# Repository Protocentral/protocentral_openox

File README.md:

Protocentral OpenOx Wireless Pulse Sensor Kit based on AFE4400/ESP32
========================================

## Don't have one? [Buy it here](https://protocentral.com/product/protocentral-openox-pulse-oximeter-breakout-board-kit/)

Protocentral OpenOx is a new standalone, wireless pulse oximetry breakout board that is powered by the ubiquitous ESP32 WROOM32 module and uses the AFE4490 IC to measure oxygen levels in the blood while also providing a PPG waveform, heart rate, and SpO2 values measured with high precision. 

Protocentral OpenOx redefines mobility and wireless capabilities. It functions as a data acquisition system, allowing for continuous real-time monitoring of blood oxygen levels via BLE, which improves the user's medical care within his or her environment as well as medical research opportunities. The standard Nellcor probe is used, which is comfortable to wear, does not restrict the user's freedom of movement, and functions as a battery-powered standalone device.

## Hardware Setup

Connection with the Arduino board is as follows:

 |OpenOx pin label| Arduino Connection  |Pin Function      |
 |:-----------------: |:---------------------:|:------------------:|
 | Tx0              |  -                       |  Serial Data     |
 | RX0              |  -                        |  Serial Clock    |
 | SDA              |  SDA                        |  Power           |
 | SCL              |  SCL                      |  GND             |
 | GND              | GND                     |  Ground          |
 | 3V3              | 3V                      |  3V power supply |

# Visualizing Output

### USB Streaming

* Open the GUI, make sure to select **AFE4490 breakout** under the **Board** dropdown and the appropriate **Port**. If everything goes well, you will be able to see the screen as pictured above.

   <center>

  </center>

### BLE streaming

 <center>

  </center>

 <center>

  </center>

## For further details, refer [the documentation on OpenOx Wireless Pulse Sensor](https://docs.protocentral.com/getting-started-with-openox/)

License Information
===================

This product is open source! Both, our hardware and software are open source and licensed under the following licenses:

Hardware
---------

**All hardware is released under the [CERN-OHL-P v2](https://ohwr.org/cern_ohl_p_v2.txt)** license.

Copyright CERN 2020.

This source describes Open Hardware and is licensed under the CERN-OHL-P v2.

You may redistribute and modify this documentation and make products
using it under the terms of the CERN-OHL-P v2 (https:/cern.ch/cern-ohl).
This documentation is distributed WITHOUT ANY EXPRESS OR IMPLIED
WARRANTY, INCLUDING OF MERCHANTABILITY, SATISFACTORY QUALITY
AND FITNESS FOR A PARTICULAR PURPOSE. Please see the CERN-OHL-P v2
for applicable conditions

Software
--------

**All software is released under the MIT License(http://opensource.org/licenses/MIT).**

THE SOFTWARE IS PROVIDED "AS IS", WITHOUT WARRANTY OF ANY KIND, EXPRESS OR IMPLIED, INCLUDING BUT NOT LIMITED TO THE WARRANTIES OF MERCHANTABILITY, FITNESS FOR A PARTICULAR PURPOSE AND NONINFRINGEMENT. IN NO EVENT SHALL THE AUTHORS OR COPYRIGHT HOLDERS BE LIABLE FOR ANY CLAIM, DAMAGES OR OTHER LIABILITY, WHETHER IN AN ACTION OF CONTRACT, TORT OR OTHERWISE, ARISING FROM, OUT OF OR IN CONNECTION WITH THE SOFTWARE OR THE USE OR OTHER DEALINGS IN THE SOFTWARE.

Documentation
-------------
**All documentation is released under [Creative Commons Share-alike 4.0 International](http://creativecommons.org/licenses/by-sa/4.0/).**

You are free to:

* Share — copy and redistribute the material in any medium or format
* Adapt — remix, transform, and build upon the material for any purpose, even commercially.
The licensor cannot revoke these freedoms as long as you follow the license terms.

Under the following terms:

* Attribution — You must give appropriate credit, provide a link to the license, and indicate if changes were made. You may do so in any reasonable manner, but not in any way that suggests the licensor endorses you or your use.
* ShareAlike — If you remix, transform, or build upon the material, you must distribute your contributions under the same license as the original.

Please check [*LICENSE.md*](LICENSE.md) for detailed license descriptions.

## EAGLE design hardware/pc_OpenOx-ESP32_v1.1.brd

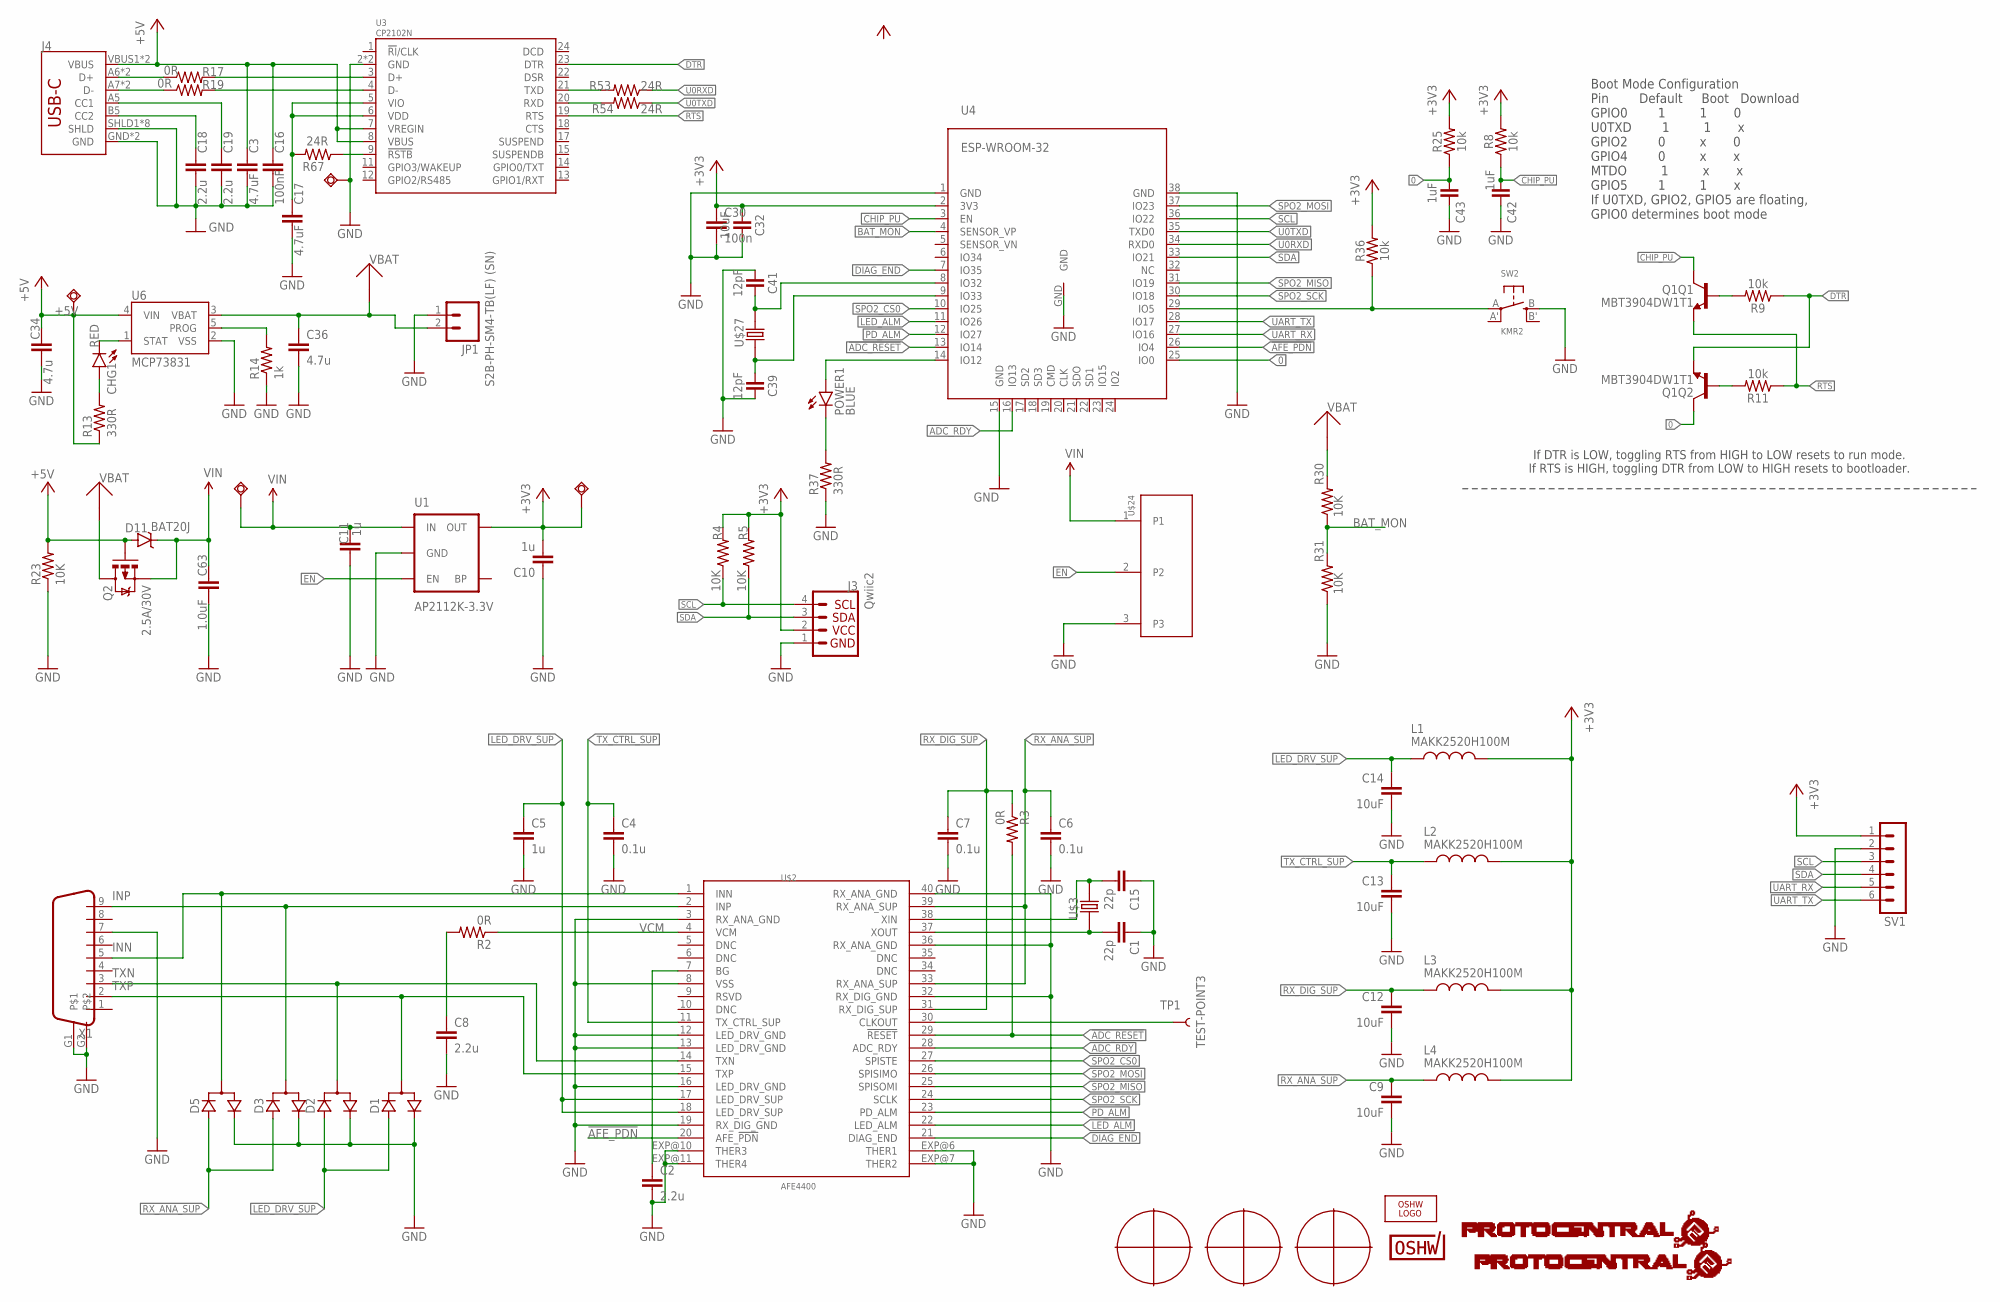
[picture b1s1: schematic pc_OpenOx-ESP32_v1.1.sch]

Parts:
C1, C15: 22p; C0402
C2, C8, C18, C19: 2.2u; C0402
C3, C17: 4.7uF; C0402
C4, C6, C7: 0.1u; C0805
C5, C10, C11: 1u; C0805
C9, C12, C13, C14, C32: 10uF; C0805
C16: 100nF; C0402
C30: 100n; C0805
C34, C36: 4.7u; C0805
C39, C41: 12pF; C0402
C42, C43: 1uF; C0402
C63: 1.0uF; C0402
CHG1: RED; CHIPLED_0603
D1, D2, D3, D5: D_ACACSOT323; SOT323
D11: BAT20J; SOD-323
J3: Qwiic2; 1X04_1MM_RA
J4: USB_C2-LAYER; USB-C-16P
JP1: S2B-PH-SM4-TB(LF) (SN); JST-2-SMD
L1, L2, L3, L4: MAKK2520H100M; INDC2520X100N
LOGO2: OSHW_LOGO_FILLX0200-NT; OSHW_FILLX200_NOTEXT
POWER1: BLUE; CHIPLED_0603
Q1: MBT3904DW1T1; SC70-6
Q2: 2.5A/30V; SOT23-3
R2, R17, R19: 0R; R0402
R3: 0R; R0805
R4, R5, R23, R30, R31: 10K; R0402
R8, R9, R11, R25, R36: 10k; 0603
R13, R37: 330R; R0402
R14: 1k; R0402
R53, R54, R67: 24R; R0402
SV1: MA06-1
SW2: KMR2; BTN_KMR2_4.6X2.8
SWIO1, SWIO2, SWIO3, SWIO17: TPSQTP13R; TP13R
TP1: TEST-POINT3; PAD.03X.03
U1: AP2112K-3.3V; SOT23-5
U3: CP2102N; QFN24
U4: ESP-WROOM-32
U6: MCP73831; SOT23-5
U$2: AFE4400; QFN-40
U$3: ABM3
U$4: PROTY_LOGO_WITH_TEXT; PROTY_WITH_TEXT
U$5: PROTY-LOGO; LOGO-PROTY
U$7: CERT-SMALL; CERT-SMALL-SILK
U$24: JS102011SCQN
U$27: 520-327-12.5-34B(32.768KHZ); ECX-31B
U$33, U$34, U$35: FUDCIALPOINTS; FIDUCIALPOINTS
X1: DB9

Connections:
0: C43.1, Q1.6 (C), R25.1, U4.25 (IO0)
3.3V: C17.1, R67.2, U3.5 (VIO), U3.6 (VDD)
!ADC_RESET: R3.2, U4.13 (IO14), U$2.29 (!RESET)
!AFE_PDN: U4.26 (IO4), U$2.20 (AFE_!PDN)
+3V3: C10.2, C30.1, C32.1, J3.2, L1.2, L2.2, L3.2, L4.2, R4.2, R5.2, R8.2, R25.2, R36.2, SV1.1, SWIO1.TP, U1.5 (OUT), U4.2 (3V3)
+5V: C3.1, C16.1, C34.1, D11.A, J4.VBUS1 (VBUS), J4.VBUS2 (VBUS), Q2.1 (G), R13.1, R23.2, SWIO3.TP, U3.7 (VREGIN), U3.8 (VBUS), U6.4 (VIN)
ADC_RDY: U4.16 (IO13), U$2.28 (ADC_RDY)
BAT_MON: R30.1, R31.2, U4.4 (SENSOR_VP)
CHIP_PU: C42.1, Q1.3 (C), R8.1, U4.3 (EN)
DIAG_END: U4.7 (IO35), U$2.21 (DIAG_END)
DTR: Q1.1 (E), R9.1, U3.23 (DTR)
EN: U1.3 (EN), U$24.2
GND: C1.1, C2.2, C3.2, C4.2, C5.2, C6.2, C7.2, C8.2, C9.2, C10.1, C11.1, C12.2, C13.2, C14.2, C15.1, C16.2, C17.2, C18.2, C19.2, C30.2, C32.2, C34.2, C36.2, C39.2, C41.1, C42.2, C43.2, C63.2, D1.2 (C), D2.2 (C), D3.2 (C), D5.2 (C), J3.1, J4.GND, J4.GND2 (GND), J4.SHLD1 (SHLD), J4.SHLD2 (SHLD), J4.SHLD3 (SHLD), J4.SHLD4 (SHLD), J4.SHLD5 (SHLD), J4.SHLD6 (SHLD), J4.SHLD7 (SHLD), J4.SHLD8 (SHLD), JP1.1, R14.1, R23.1, R31.1, R37.1, SV1.2, SW2.B (S), SWIO17.TP, U1.2 (GND), U3.2 (GND), U3.PAD (GND), U4.1 (GND), U4.15 (GND), U4.38 (GND), U4.GND, U6.2 (VSS), U$2.3 (RX_ANA_GND), U$2.8 (VSS), U$2.12 (LED_DRV_GND), U$2.13 (LED_DRV_GND), U$2.16 (LED_DRV_GND), U$2.19 (RX_DIG_GND), U$2.32 (RX_DIG_GND), U$2.36 (RX_ANA_GND), U$2.40 (RX_ANA_GND), U$2.EXP@6 (THER1), U$2.EXP@7 (THER2), U$2.EXP@10 (THER3), U$2.EXP@11 (THER4), U$24.3, X1.7, X1.G1, X1.G2
INN: D5.1 (CA), U$2.1 (INN), X1.5
INP: D3.1 (CA), U$2.2 (INP), X1.9
LED_ALM: U4.11 (IO26), U$2.22 (LED_ALM)
LED_DRV_SUP: C5.1, C14.1, D1.3 (A), D2.3 (A), L1.1, U$2.17 (LED_DRV_SUP), U$2.18 (LED_DRV_SUP)
unnamed: C1.2, U$2.37 (XOUT), U$3.1
unnamed: R67.1, U3.9 (!RSTB)
unnamed: C8.1, R2.2
unnamed: C19.1, J4.A5 (CC1)
unnamed: C18.1, J4.B5 (CC2)
unnamed: R17.2, U3.3 (D+)
unnamed: R19.2, U3.4 (D-)
unnamed: J4.A6 (D+), J4.B6 (D+), R17.1
unnamed: C15.2, U$2.38 (XIN), U$3.2
unnamed: C2.1, U$2.7 (BG)
unnamed: J4.A7 (D-), J4.B7 (D-), R19.1
unnamed: TP1.P$1, U$2.30 (CLKOUT)
unnamed: Q1.5 (B), R9.2
unnamed: Q1.2 (B), R11.2
unnamed: CHG1.C, U6.1 (STAT)
unnamed: CHG1.A, R13.2
unnamed: R14.2, U6.5 (PROG)
unnamed: C41.2, U4.8 (IO32), U$27.P$2 (2)
unnamed: C39.1, U4.9 (IO33), U$27.P$1 (1)
unnamed: R36.1, SW2.A, U4.29 (IO5)
unnamed: POWER1.A, U4.14 (IO12)
unnamed: POWER1.C, R37.2
PD_ALM: U4.12 (IO27), U$2.23 (PD_ALM)
RTS: Q1.4 (E), R11.1, U3.19 (RTS)
RX: R54.2, U3.20 (RXD)
RX_ANA_SUP: C6.1, C9.1, D3.3 (A), D5.3 (A), L4.1, U$2.33 (RX_ANA_SUP), U$2.39 (RX_ANA_SUP)
RX_DIG_SUP: C7.1, C12.1, L3.1, R3.1, U$2.31 (RX_DIG_SUP)
SCL: J3.4, R4.1, SV1.3, U4.36 (IO22)
SDA: J3.3, R5.1, SV1.4, U4.33 (IO21)
SPO2_CS0: U4.10 (IO25), U$2.27 (SPISTE)
SPO2_MISO: U4.31 (IO19), U$2.25 (SPISOMI)
SPO2_MOSI: U4.37 (IO23), U$2.26 (SPISIMO)
SPO2_SCK: U4.30 (IO18), U$2.24 (SCLK)
TX: R53.2, U3.21 (TXD)
TXN: D2.1 (CA), U$2.14 (TXN), X1.3
TXP: D1.1 (CA), U$2.15 (TXP), X1.2
TX_CTRL_SUP: C4.1, C13.1, L2.1, U$2.11 (TX_CTRL_SUP)
U0RXD: R53.1, U4.34 (RXD0)
U0TXD: R54.1, U4.35 (TXD0)
UART_RX: SV1.5, U4.27 (IO16)
UART_TX: SV1.6, U4.28 (IO17)
VBAT: C36.1, JP1.2, Q2.3 (D), R30.2, U6.3 (VBAT)
VCM: R2.1, U$2.4 (VCM)
VIN: C11.2, C63.1, D11.C, Q2.2 (S), SWIO2.TP, U1.1 (IN), U$24.1

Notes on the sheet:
Boot Mode Configuration Pin Default Boot Download GPIO0 1 1 0 U0TXD 1 1 x GPIO2 0 x 0 GPIO4 0 x x MTDO 1 x x GPIO5 1 1 x If U0TXD, GPIO2, GPIO5 are floating, GPIO0 determines boot mode
If DTR is LOW, toggling RTS from HIGH to LOW resets to run mode. If RTS is HIGH, toggling DTR from LOW to HIGH resets to bootloader.

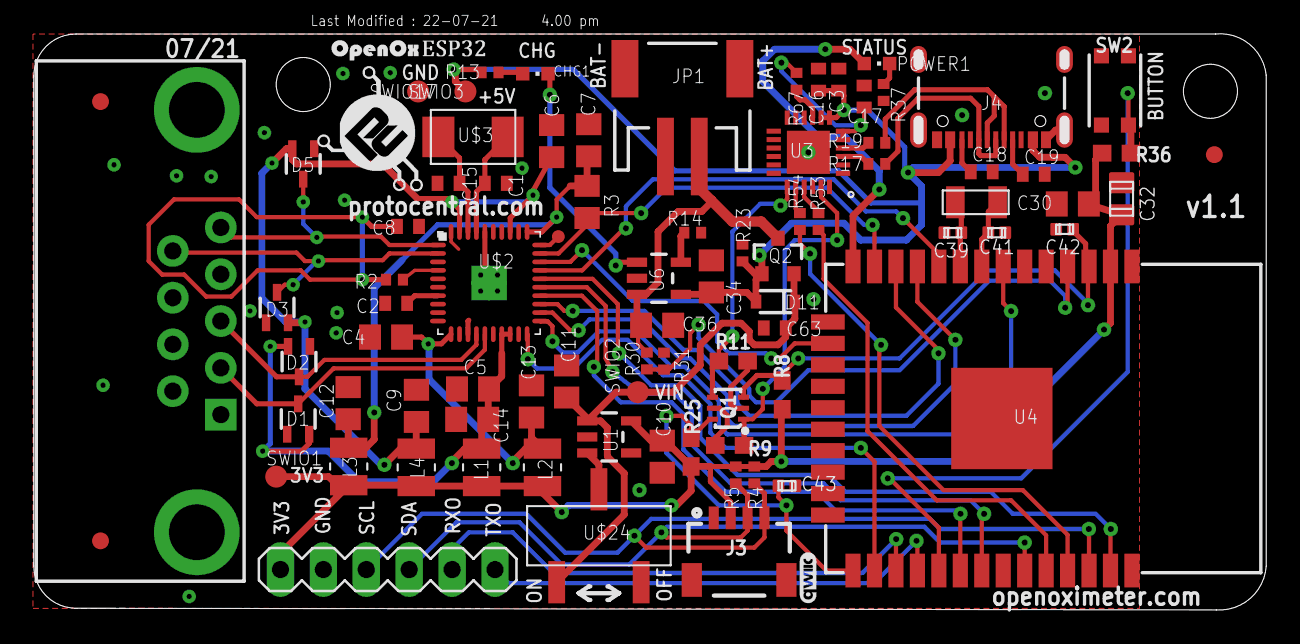
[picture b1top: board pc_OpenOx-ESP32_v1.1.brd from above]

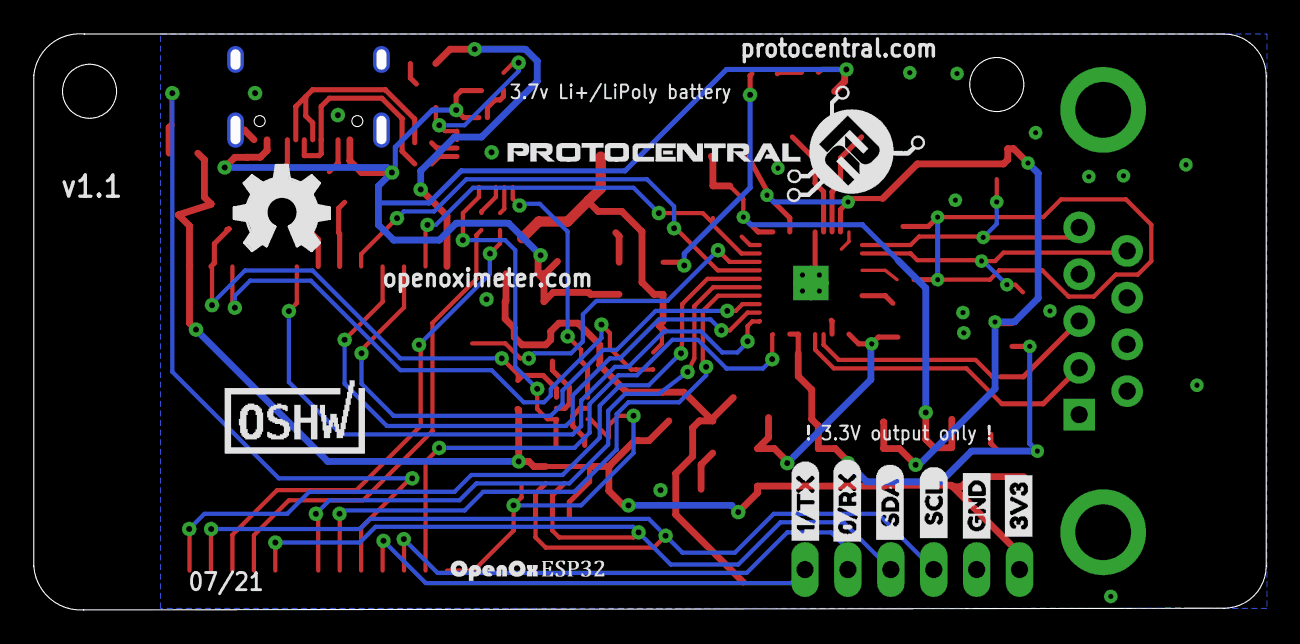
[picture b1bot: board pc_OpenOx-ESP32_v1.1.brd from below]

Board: 4 copper layers, 72.4 x 33.5 mm, 97 parts (11 on the bottom side), 61 nets.

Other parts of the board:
LOGO4: QWIIC_LOGO_3MM; QWIIC_3MM
U$6: 3V32
U$8, U$12: OPENOXLOGO1
U$9: _SCL16
U$10: _SDA17
U$13: GND0
U$16: PULSE
U$44: 1#TX1
U$48: 0#RX0

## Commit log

2022-11-27 Added firmware
2022-11-30 Added breakout image
2024-12-10 Updated the folder name and workflow, readme
2024-12-10 Updated image
2025-04-09 files renamed
2025-04-09 main.yml updated
2025-04-09 project type added
2025-04-10 arduino lint actions removed
2025-04-10 Readme updated
2025-04-10 compile-examples.yml sketch paths updated

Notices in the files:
README.md:
CC-BY-SA-4.0
parts and their libraries:
SparkFun-PowerIC: Licensing: Creative Commons ShareAlike 4.0 International - https://creativecommons.org/licenses/by-sa/4.0
